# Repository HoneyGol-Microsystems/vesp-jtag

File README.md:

# 
An Open Source Hardware JTAG/UART/GPIO interface board based on the amazing [Steppenprobe](https://github.com/diegoherranz/steppenprobe) containing Pmod-compatible connector.

## Basic specs:

- Open Source Hardware and designed in [KiCad](https://kicad.org).
- Majority of footprints have easy to solder 0805 packages.
- [FT2232H](https://ftdichip.com/products/ft2232hl)-based.
- Simultaneous operation of JTAG/UART or GPIO/UART (software-configurable).
- Standard Pmod connector for direct connection to a compatible FPGA.
- Signals also available on 2.54 mm pin header to work with any custom pinout.
- USB powered: no power supply needed.
- USB type-C receptacle: more convenient (reversible) and future-proof.
- 2 GPIO and 2 user-controllable LEDs.
- I/O buffers for protection and compatible with a wide voltage range (1.65 V to 5.5 V).
- Descriptive LED indicators.
- (TODO) OpenOCD compatibility.

*Please note that the board itself is wider than the Pmod standard allows, therefore it is not entirely "Pmod compatible". It may happen that if Pmod ports on your FPGA board are too close to each other, another Pmod board will not fit next to the vesp-jtag at the same time.*

## Schematic PDF, Gerbers and other generated files:
See [releases](https://github.com/HoneyGol-Microsystems/vesp-jtag/releases).

## FTDI channels

The FT2232H has 2 independent channels. In this board:

- Channel A: Used as a JTAG or GPIOs
- Channel B: Used as an UART.

After enumeration, both channels will default to the UART mode, so on a Linux system they will show up as `/dev/ttyUSB0` and `/dev/ttyUSB1`. When the channel A gets reconfigured to a MPSSE mode (e.g. when using OpenOCD with it), then `/dev/ttyUSB0` will disappear and the channel B will remain as `/dev/ttyUSB1`.

## 3D renders

## OpenOCD example commands
TODO

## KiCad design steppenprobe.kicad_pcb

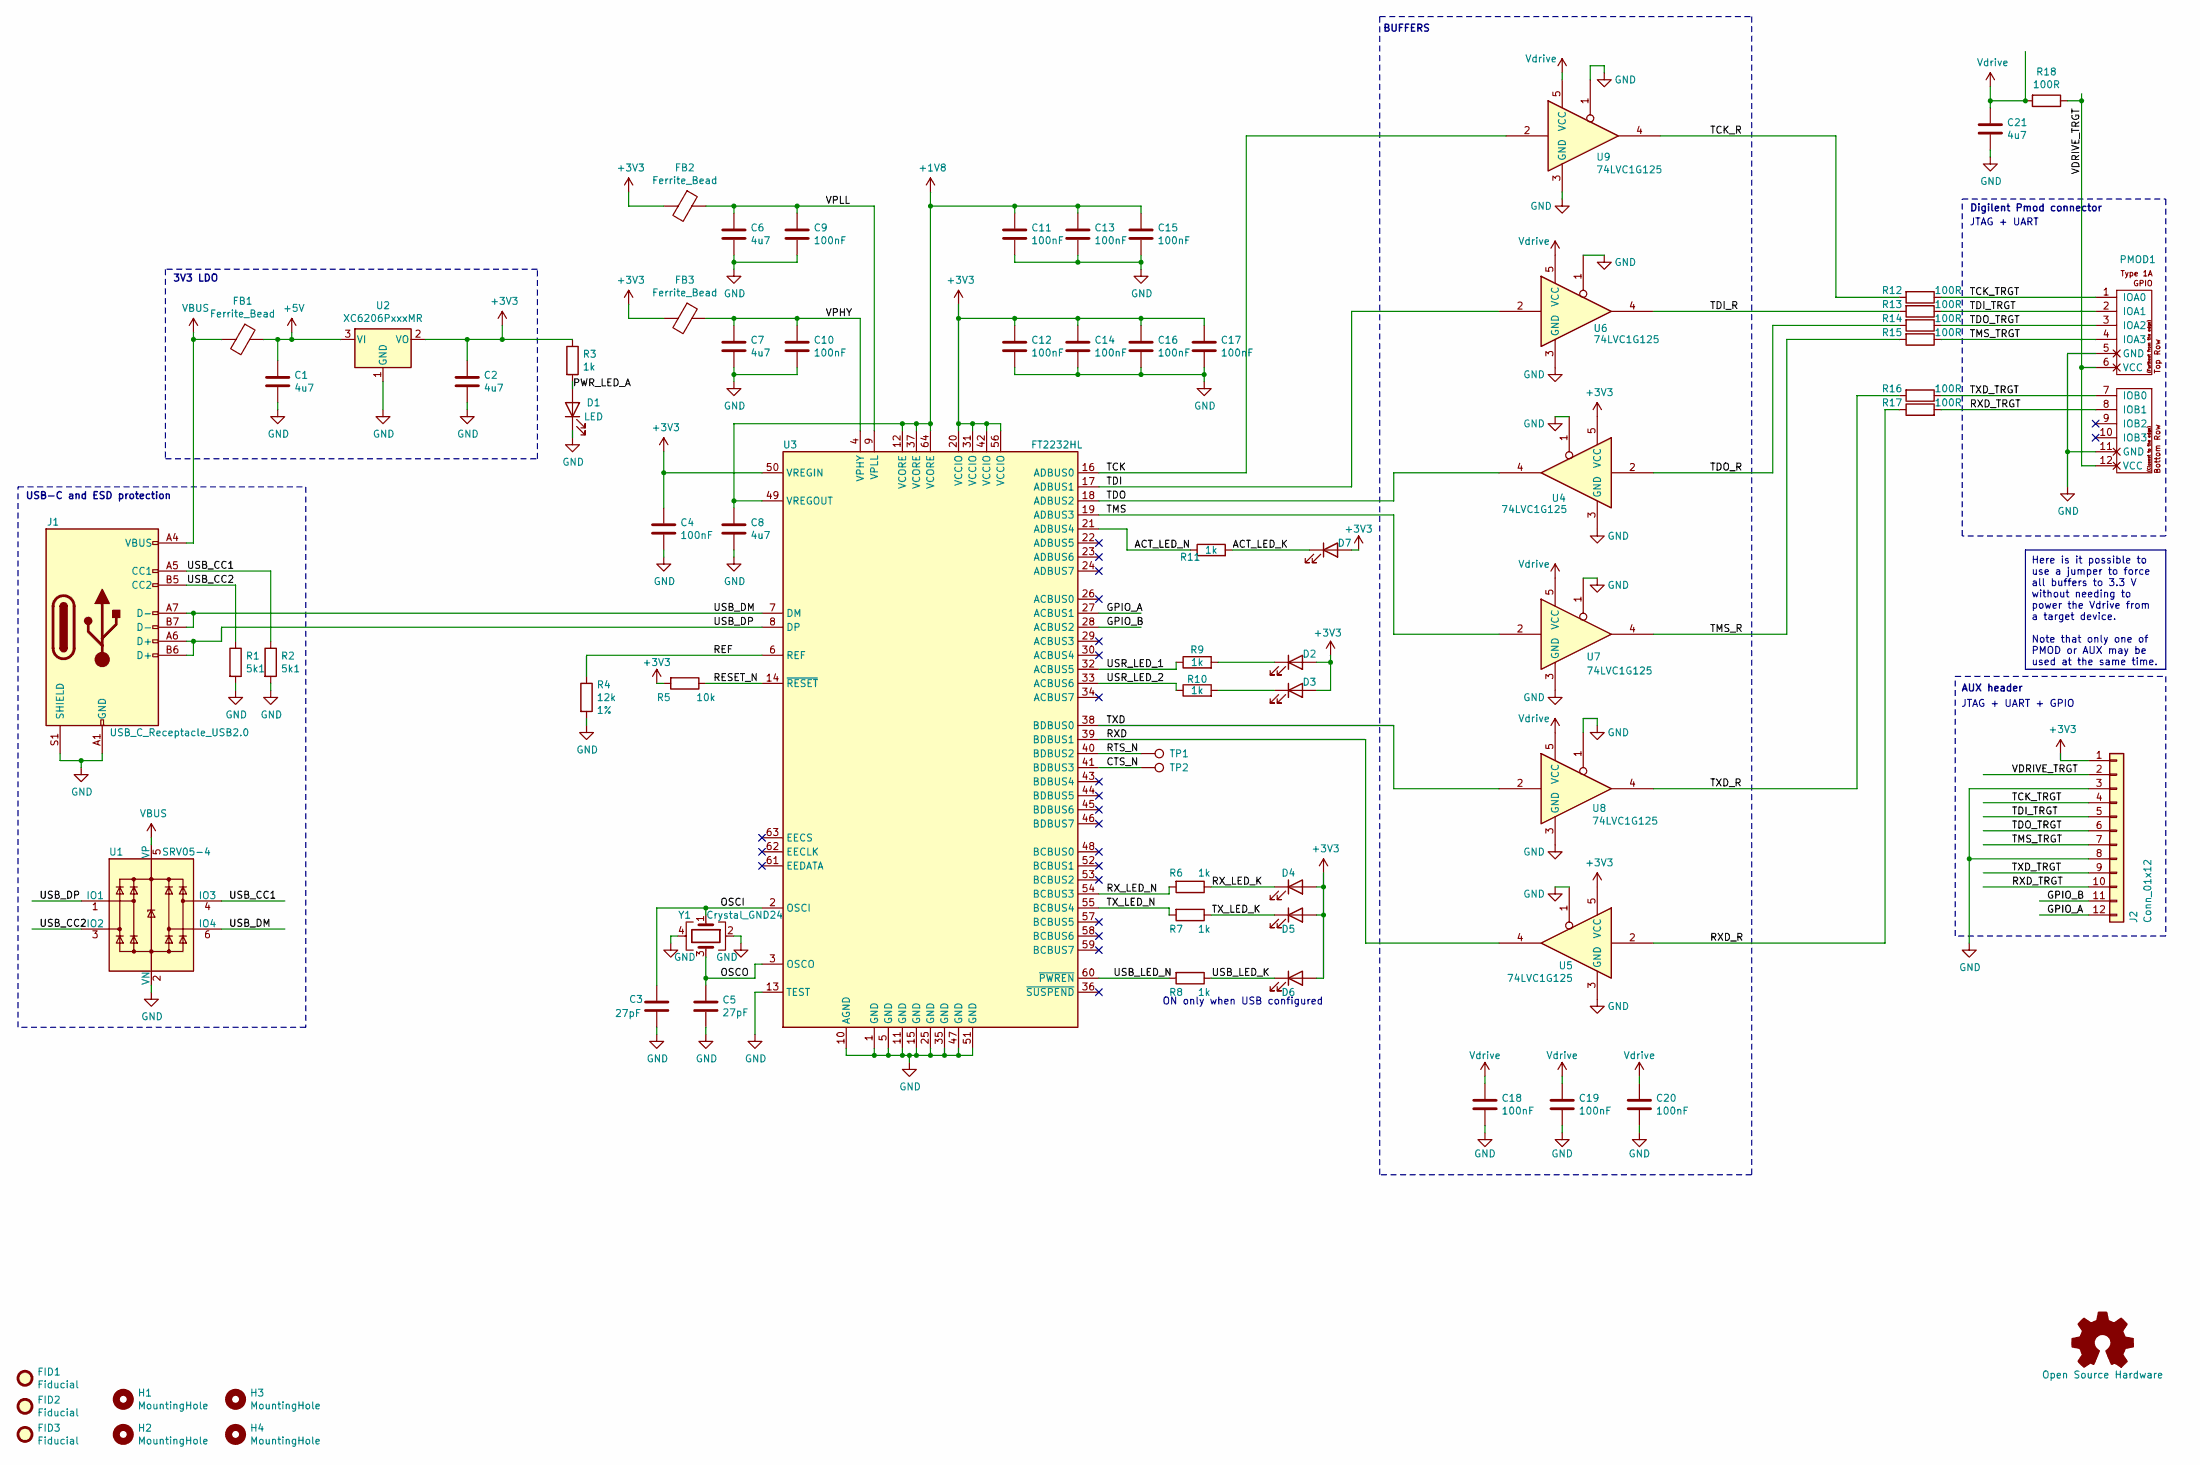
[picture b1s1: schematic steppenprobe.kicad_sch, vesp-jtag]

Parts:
C1, C2, C6, C7, C8, C21: 4u7; C_0805_2012Metric; Tolerance 10%; MPN CL10A475KO8NNNC; LCSC_PN C19666
C3, C5: 27pF; C_0805_2012Metric; Tolerance 5%; MPN C0603C270J5GAC; LCSC_PN C1656
C4, C9, C10, C11, C12, C13, C14, C15, C16, C17, C18, C19, C20: 100nF; C_0805_2012Metric; Tolerance 10%; MPN CC0603KRX7R9BB104; LCSC_PN C14663
D1, D4, D5, D6, D7: LED; LED_0805_2012Metric; MPN 19-217/GHC-YR1S2/3T; LCSC_PN C72043
D2, D3: LED; LED_0805_2012Metric
FB1, FB2, FB3: Ferrite_Bead; L_0805_2012Metric; MPN2 BKP1608HS121-T; LCSC_PN C85831
FID1, FID2, FID3: Fiducial; Fiducial_1mm_Mask2mm
H1, H2, H3, H4: MountingHole; MountingHole_3.2mm_M3
J1: USB_C_Receptacle_USB2.0; USB_C_Receptacle_GCT_USB4085; MPN USB4085-GF-A
J2: Conn_01x12; PinHeader_1x12_P2.54mm_Vertical
LOGO1: Open Source Hardware; OSHW-Logo_7.5x8mm_SilkScreen
PMOD1: PMOD-Device-x2-Type-1A-GPIO; pmod_pin_array_6x2
R1, R2: 5k1; R_0805_2012Metric; Tolerance 5%; LCSC_PN C23186
R3, R6, R7, R8, R11: 1k; R_0805_2012Metric; Tolerance 5%; LCSC_PN C21190
R4: 12k; R_0805_2012Metric; Tolerance 1%; LCSC_PN C22790
R5: 10k; R_0805_2012Metric; Tolerance 5%; LCSC_PN C25804
R9, R10: 1k; R_0805_2012Metric
R12, R13, R14, R15, R16, R17, R18: 100R; R_0805_2012Metric; Tolerance 5%; LCSC_PN C22775
TP1, TP2: TestPoint; TestPoint_Pad_D1.0mm
U1: SRV05-4; SOT-23-6; MPN2 SRV05-4-P-T7; LCSC_PN C85364
U2: XC6206PxxxMR; SOT-23-3; MPN XC6206P332MR; LCSC_PN C5446
U3: FT2232HL; LQFP-64_10x10mm_P0.5mm; MPN FT2232HL; LCSC_PN C27882
U4, U5, U6, U7, U8, U9: 74LVC1G125; SOT-353_SC-70-5; MPN 74LVC1G125GW,125; LCSC_PN C12519
Y1: Crystal_GND24; Crystal_SMD_3225-4Pin_3.2x2.5mm; Tolerance 10PPM; MPN ABM8-12.000MHZ-20-B1U-T; LCSC_PN C9002

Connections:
+1V8: C8.1, C11.1, C13.1, C15.1, U3.12 (VCORE), U3.37 (VCORE), U3.49 (VREGOUT), U3.64 (VCORE)
+3V3: C2.1, C4.1, C12.1, C14.1, C16.1, C17.1, D2.2 (A), D3.2 (A), D4.2 (A), D5.2 (A), D6.2 (A), D7.2 (A), FB2.2, FB3.2, J2.1, R3.1, R5.2, U2.2 (VO), U3.20 (VCCIO), U3.31 (VCCIO), U3.42 (VCCIO), U3.50 (VREGIN), U3.56 (VCCIO), U4.5 (VCC), U5.5 (VCC)
+5V: C1.1, FB1.1, U2.3 (VI)
/ACT_LED_K: D7.1 (K), R11.2
/ACT_LED_N: R11.1, U3.21 (ADBUS4)
/CTS_N: TP2.1, U3.41 (BDBUS3)
/GPIO_A: J2.12, U3.27 (ACBUS1)
/GPIO_B: J2.11, U3.28 (ACBUS2)
/OSCI: C3.1, U3.2 (OSCI), Y1.1
/OSCO: C5.1, U3.3 (OSCO), Y1.3
/PWR_LED_A: D1.2 (A), R3.2
/REF: R4.1, U3.6 (REF)
/RESET_N: R5.1, U3.14 (~RESET)
/RTS_N: TP1.1, U3.40 (BDBUS2)
/RXD: U3.39 (BDBUS1), U5.4
/RXD_R: R17.1, U5.2
/RXD_TRGT: J2.10, PMOD1.8 (IOB1), R17.2
/RX_LED_K: D4.1 (K), R6.1
/RX_LED_N: R6.2, U3.54 (BCBUS3)
/TCK: U3.16 (ADBUS0), U9.2
/TCK_R: R12.2, U9.4
/TCK_TRGT: J2.4, PMOD1.1 (IOA0), R12.1
/TDI: U3.17 (ADBUS1), U6.2
/TDI_R: R13.2, U6.4
/TDI_TRGT: J2.5, PMOD1.2 (IOA1), R13.1
/TDO: U3.18 (ADBUS2), U4.4
/TDO_R: R14.2, U4.2
/TDO_TRGT: J2.6, PMOD1.3 (IOA2), R14.1
/TMS: U3.19 (ADBUS3), U7.2
/TMS_R: R15.2, U7.4
/TMS_TRGT: J2.7, PMOD1.4 (IOA3), R15.1
/TXD: U3.38 (BDBUS0), U8.2
/TXD_R: R16.2, U8.4
/TXD_TRGT: J2.9, PMOD1.7 (IOB0), R16.1
/TX_LED_K: D5.1 (K), R7.1
/TX_LED_N: R7.2, U3.55 (BCBUS4)
/USB_CC1: J1.A5 (CC1), R2.1, U1.4 (IO3)
/USB_CC2: J1.B5 (CC2), R1.1, U1.3 (IO2)
/USB_DM: J1.A7 (D-), J1.B7 (D-), U1.6 (IO4), U3.7 (DM)
/USB_DP: J1.A6 (D+), J1.B6 (D+), U1.1 (IO1), U3.8 (DP)
/USB_LED_K: D6.1 (K), R8.1
/USB_LED_N: R8.2, U3.60 (~PWREN)
/USR_LED_1: R9.1, U3.32 (ACBUS5)
/USR_LED_2: R10.1, U3.33 (ACBUS6)
/VDRIVE_TRGT: J2.2, PMOD1.6 (VCC), PMOD1.12 (VCC), R18.1
/VPHY: C7.1, C10.1, FB3.1, U3.4 (VPHY)
/VPLL: C6.1, C9.1, FB2.1, U3.9 (VPLL)
GND: C1.2, C2.2, C3.2, C4.2, C5.2, C6.2, C7.2, C8.2, C9.2, C10.2, C11.2, C12.2, C13.2, C14.2, C15.2, C16.2, C17.2, C18.2, C19.2, C20.2, C21.2, D1.1 (K), J1.A1 (GND), J1.A12 (GND), J1.B1 (GND), J1.B12 (GND), J1.S1 (SHIELD), J2.3, J2.8, PMOD1.5 (GND), PMOD1.11 (GND), R1.2, R2.2, R4.2, U1.2 (VN), U2.1 (GND), U3.1 (GND), U3.5 (GND), U3.10 (AGND), U3.11 (GND), U3.13 (TEST), U3.15 (GND), U3.25 (GND), U3.35 (GND), U3.47 (GND), U3.51 (GND), U4.1, U4.3 (GND), U5.1, U5.3 (GND), U6.1, U6.3 (GND), U7.1, U7.3 (GND), U8.1, U8.3 (GND), U9.1, U9.3 (GND), Y1.2, Y1.4
unnamed: D2.1 (K), R9.2
unnamed: D3.1 (K), R10.2
VBUS: FB1.2, J1.A4 (VBUS), J1.A9 (VBUS), J1.B4 (VBUS), J1.B9 (VBUS), U1.5 (VP)
Vdrive: C18.1, C19.1, C20.1, C21.1, R18.2, U6.5 (VCC), U7.5 (VCC), U8.5 (VCC), U9.5 (VCC)

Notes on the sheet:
Here is it possible to use a jumper to force all buffers to 3.3 V without needing to power the Vdrive from a target device. Note that only one of PMOD or AUX may be used at the same time.
ON only when USB configured
JTAG + UART
3V3 LDO
AUX header
JTAG + UART + GPIO
Digilent Pmod connector
USB-C and ESD protection
BUFFERS

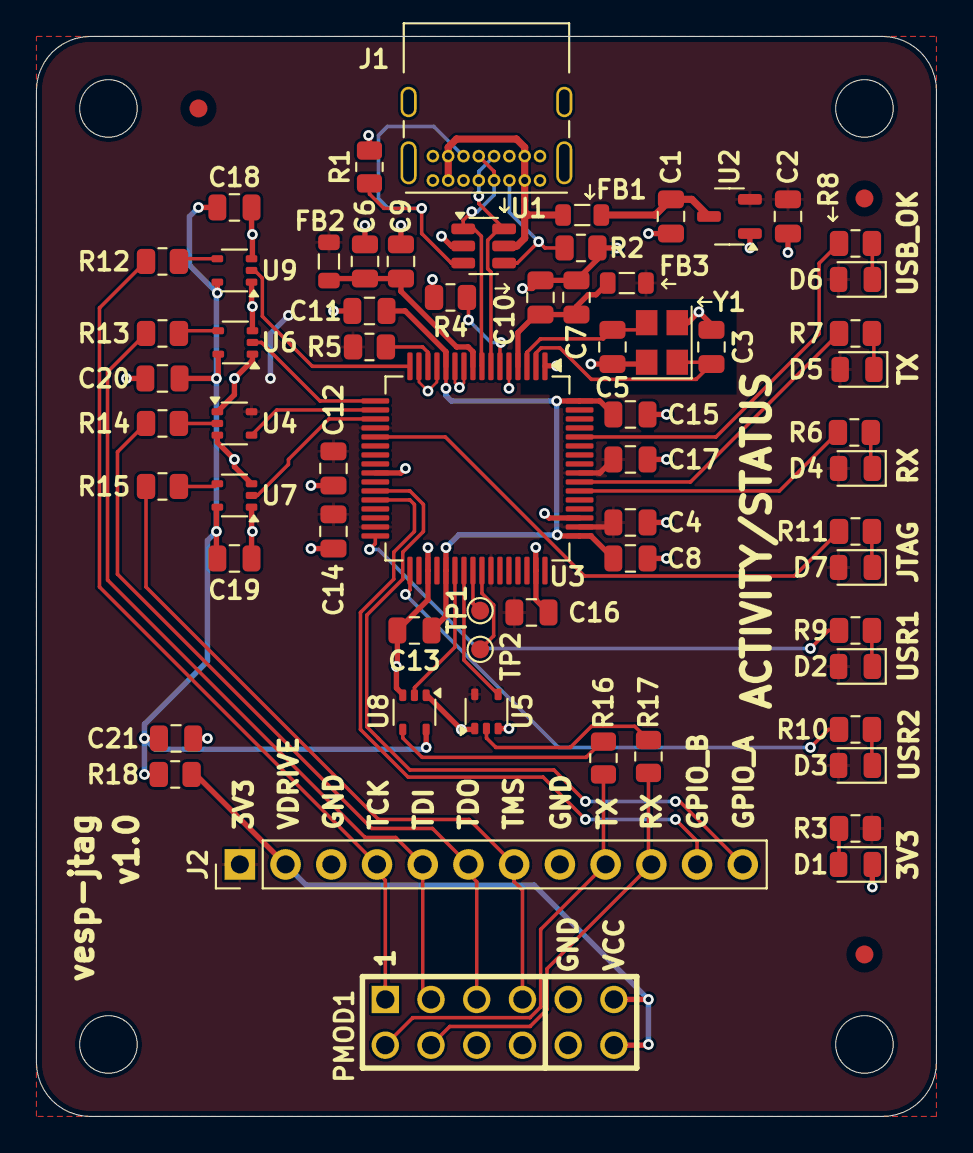
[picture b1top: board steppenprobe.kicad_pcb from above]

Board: 2 copper layers, 50.0 x 60.0 mm, 72 parts (1 on the bottom side), 52 nets.

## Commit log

2024-10-19 Removed EEPROM.
2024-10-19 Added PMOD.
2024-10-21 Added user leds, removed uneccessary connections.
2024-10-22 Fixed errors, assigned footprints.
2024-11-02 Updated footprints, removed testpoints, edited PCB layout.
2024-11-03 Updated pcb.
2024-11-04 Rotated 3V3 LED.
2024-11-04 Synced footprints.
2024-11-04 Fixed part numbering.
2024-11-04 Edited silkscreen graphics.
2024-11-04 Fixed DRC problems, added logo dir.
2024-11-05 Reworked oscillator placement. Fixed silkscreen, added arrows.
2024-11-05 Moved vias closer to pads.
2024-11-06 Moved vias, silkscreen alignment.
2024-11-12 Changed export settings.
2024-11-15 Updated part numbers.
2024-11-15 Updated README and renders.
2024-11-15 Spelling fixes
2024-11-15 Typos, spelling
2024-12-03 OpenOCD config initial commit.
